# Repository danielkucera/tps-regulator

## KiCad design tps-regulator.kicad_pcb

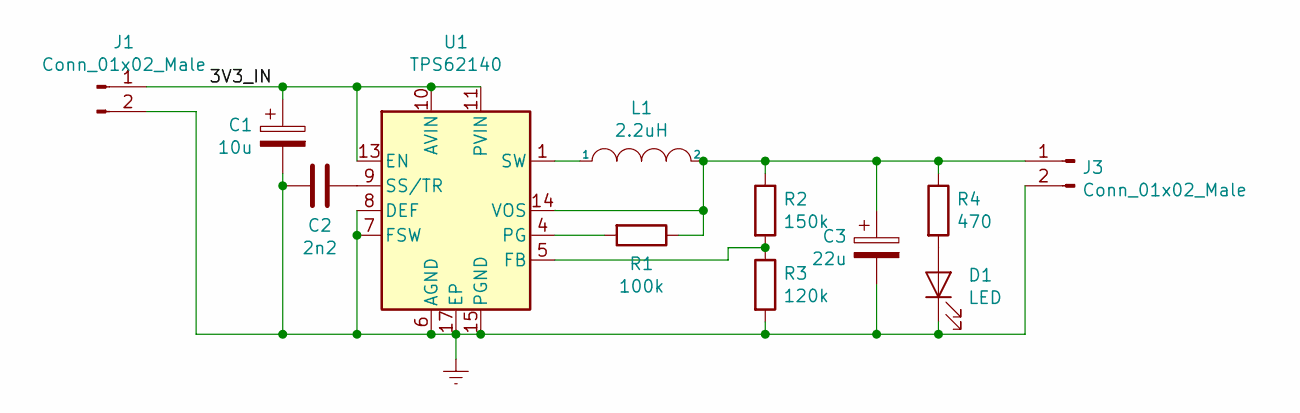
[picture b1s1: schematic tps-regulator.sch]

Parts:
C1: 10u; C_0603_1608Metric
C2: 2n2; C_0402_1005Metric
C3: 22u; C_0603_1608Metric
D1: LED; LED_0402_1005Metric
J1, J3: Conn_01x02_Male; PinHeader_1x02_P2.54mm_Vertical
L1: 2.2uH; L_6.3x6.3_H3
R1: 100k; R_0402_1005Metric
R2: 150k; R_0402_1005Metric
R3: 120k; R_0402_1005Metric
R4: 470; R_0402_1005Metric
U1: TPS62140; VQFN-16-1EP_3x3mm_P0.5mm_EP1.68x1.68mm_ThermalVias

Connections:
/3V3_IN: C1.1, J1.1, U1.10 (AVIN), U1.11 (PVIN), U1.12 (PVIN), U1.13 (EN)
Earth: C1.2, C2.2, C3.2, D1.1 (K), J1.2, J3.2, R3.2, U1.6 (AGND), U1.7 (FSW), U1.8 (DEF), U1.15 (PGND), U1.16 (PGND), U1.17 (EP)
unnamed: C2.1, U1.9 (SS/TR)
unnamed: C3.1, J3.1, L1.2, R1.1, R2.1, R4.1, U1.14 (VOS)
unnamed: D1.2 (A), R4.2
unnamed: L1.1, U1.1 (SW), U1.2 (SW), U1.3 (SW)
unnamed: R1.2, U1.4 (PG)
unnamed: R2.2, R3.1, U1.5 (FB)

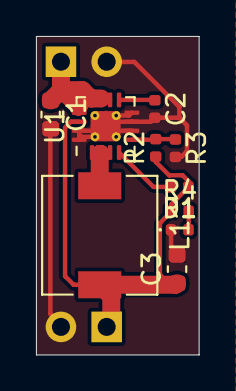
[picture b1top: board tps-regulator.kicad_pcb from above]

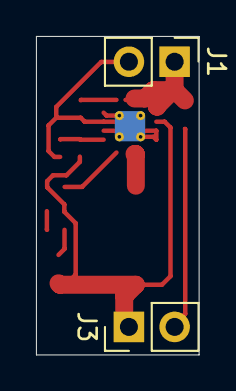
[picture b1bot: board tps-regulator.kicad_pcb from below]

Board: 2 copper layers, 9.0 x 17.7 mm, 12 parts (2 on the bottom side), 8 nets.

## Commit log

2019-12-13 v1.0
